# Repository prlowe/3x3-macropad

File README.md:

# 3x3 macropad with rotary encoder

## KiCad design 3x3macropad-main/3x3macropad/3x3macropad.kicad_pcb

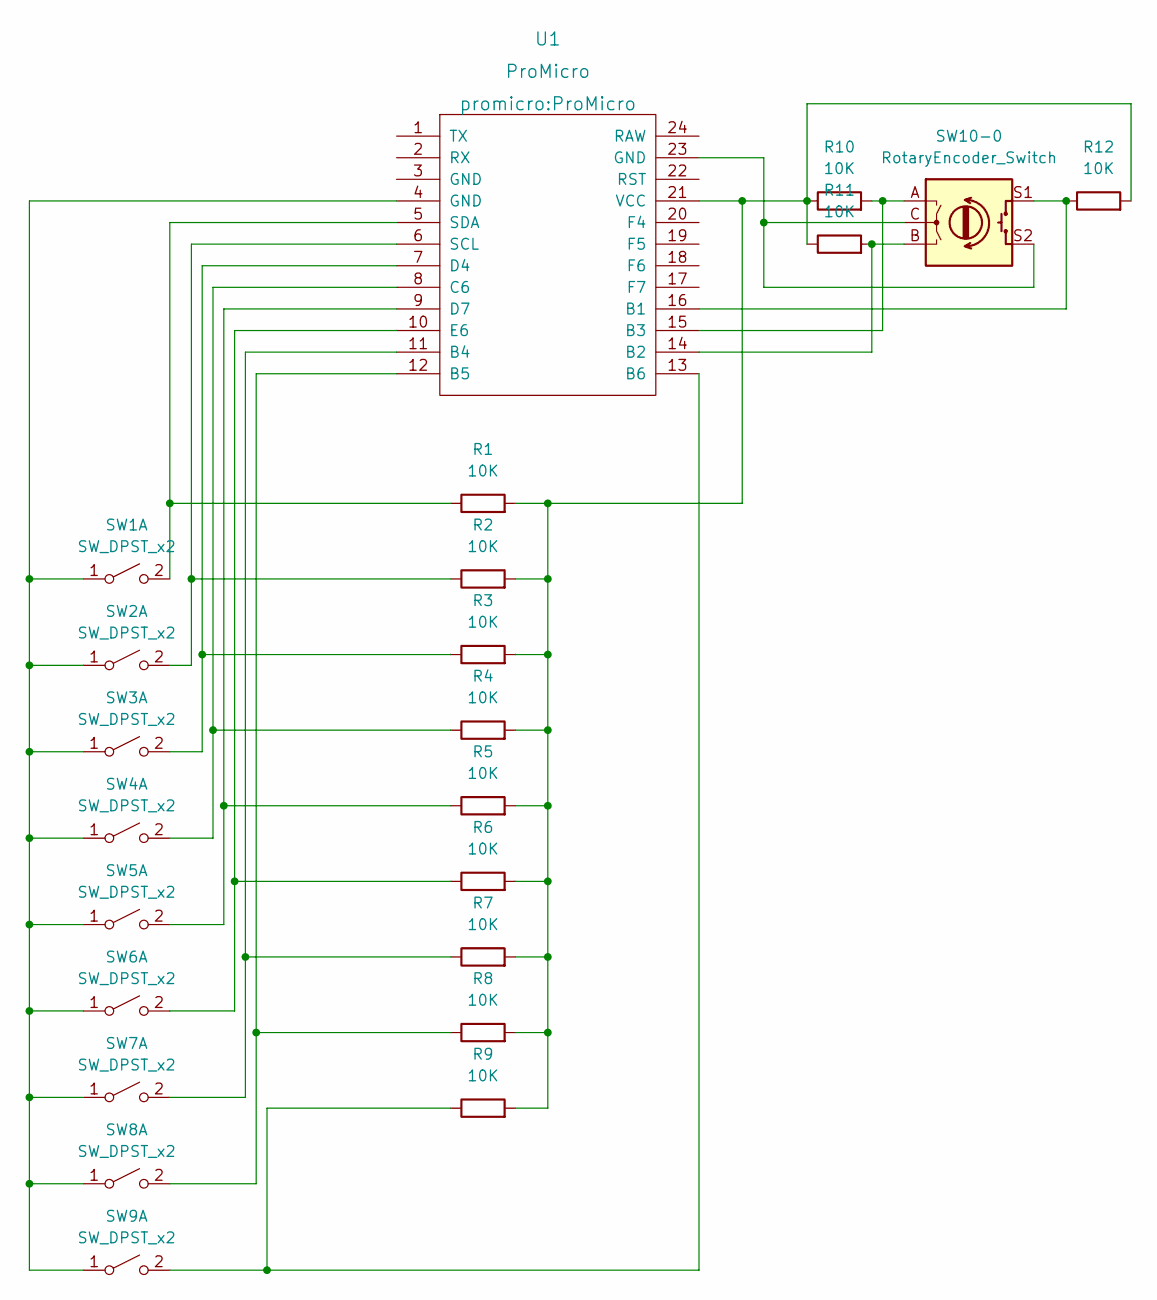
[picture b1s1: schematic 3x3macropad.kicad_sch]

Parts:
R1, R2, R3, R4, R5, R6, R7, R8, R9, R10, R11, R12: 10K; R_0805_2012Metric
SW1, SW2, SW3, SW4, SW5, SW6, SW7, SW8, SW9: SW_DPST_x2; MXOnly-1U-Hotswap
SW10-0: RotaryEncoder_Switch; RotaryEncoder_Alps_EC11E-Switch_Vertical_H20mm
U1: ProMicro

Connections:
unnamed: SW1.1 (A), SW2.1 (A), SW3.1 (A), SW4.1 (A), SW5.1 (A), SW6.1 (A), SW7.1 (A), SW8.1 (A), SW9.1 (A), U1.4 (GND)
unnamed: R1.1, SW1.2 (B), U1.5 (SDA)
unnamed: R2.1, SW2.2 (B), U1.6 (SCL)
unnamed: R3.1, SW3.2 (B), U1.7 (D4)
unnamed: R4.1, SW4.2 (B), U1.8 (C6)
unnamed: R5.1, SW5.2 (B), U1.9 (D7)
unnamed: R6.1, SW6.2 (B), U1.10 (E6)
unnamed: R7.1, SW7.2 (B), U1.11 (B4)
unnamed: R8.1, SW8.2 (B), U1.12 (B5)
unnamed: R9.1, SW9.2 (B), U1.13 (B6)
unnamed: R11.2, SW10-0.B, U1.14 (B2)
unnamed: R10.2, SW10-0.A, U1.15 (B3)
unnamed: R12.1, SW10-0.S1, U1.16 (B1)
unnamed: R1.2, R2.2, R3.2, R4.2, R5.2, R6.2, R7.2, R8.2, R9.2, R10.1, R11.1, R12.2, U1.21 (VCC)
unnamed: SW10-0.C, SW10-0.S2, U1.23 (GND)

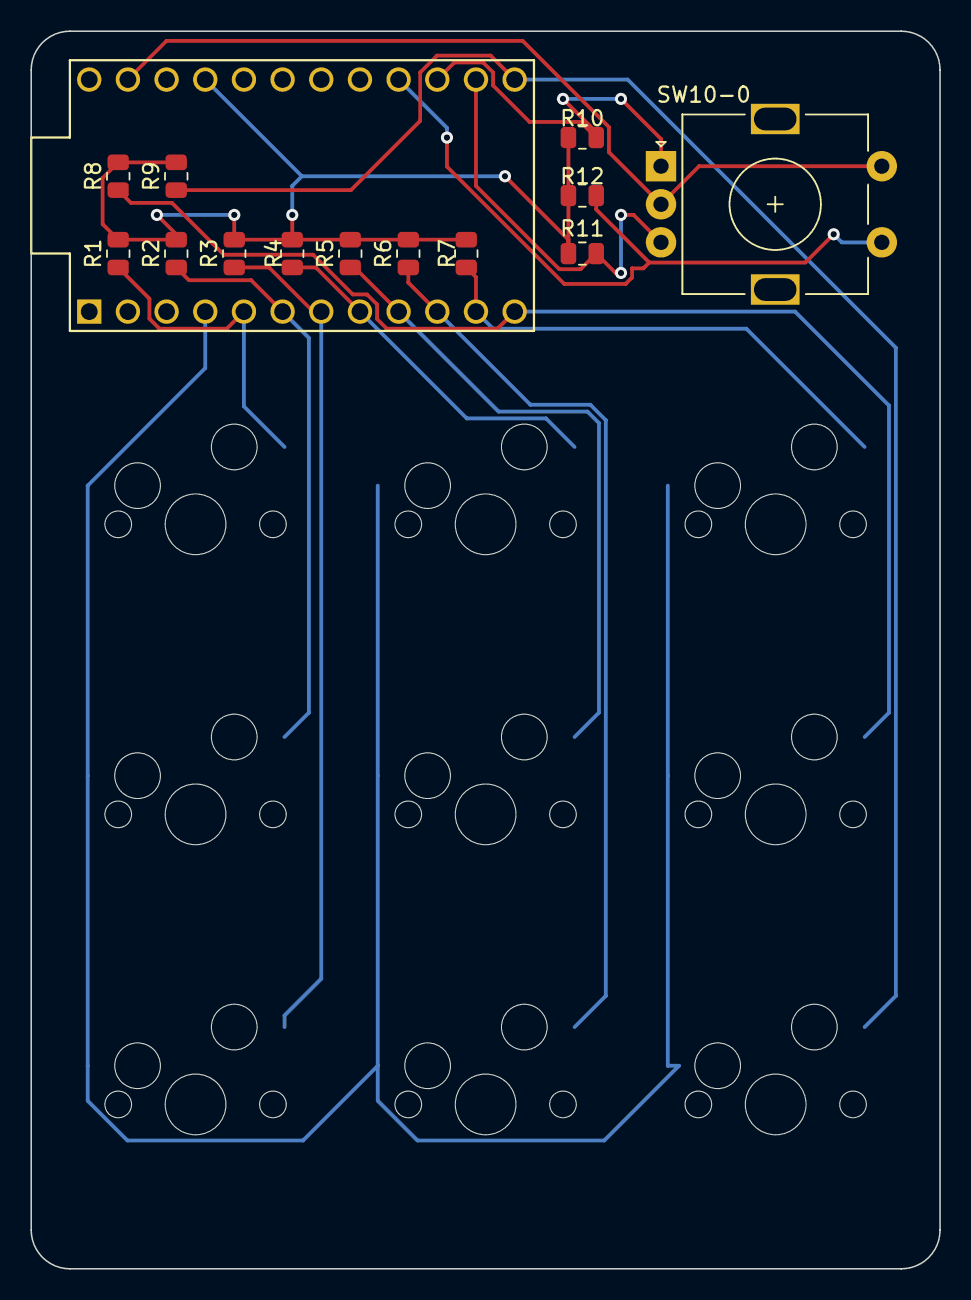
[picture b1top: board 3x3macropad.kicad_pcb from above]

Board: 2 copper layers, 59.7 x 81.3 mm, 23 parts (0 on the bottom side), 15 nets.

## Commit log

2024-11-27 new file: 3x3macropad-main/3x3macropad/3x3macropad-backups/3x3macropad-2024-11-27_131409.zip new file: 3x3macropad-main/3x3macropad/3x3macropad-backups/3x3macropad-2024-11-27_134707.zip new file: 3x3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
